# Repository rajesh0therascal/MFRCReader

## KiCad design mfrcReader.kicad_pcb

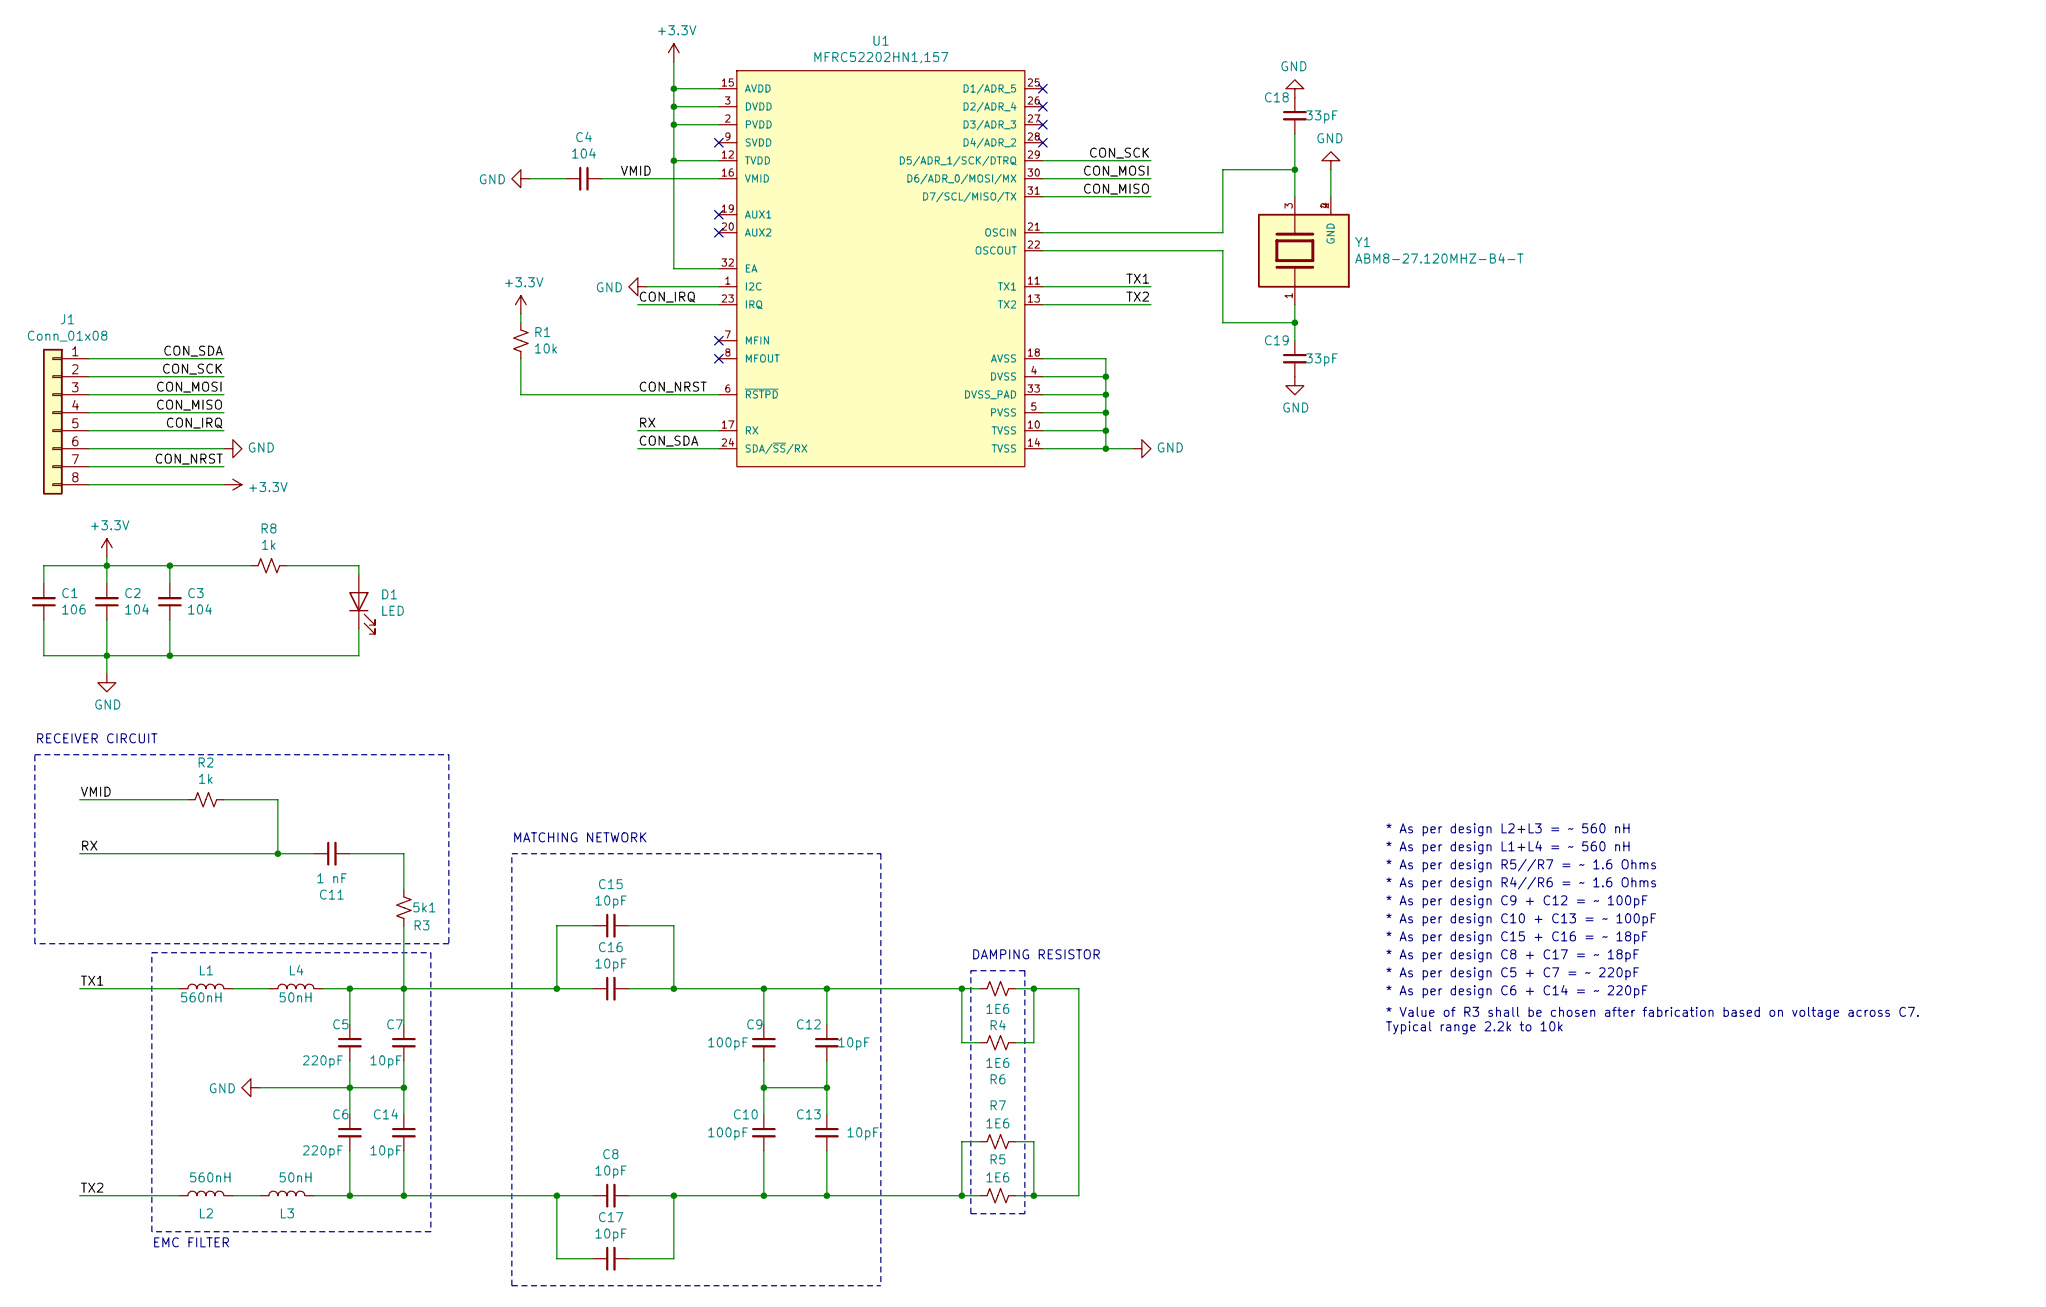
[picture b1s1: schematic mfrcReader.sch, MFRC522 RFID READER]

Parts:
C1: 106; C_0805_2012Metric_Pad1.15x1.40mm_HandSolder
C2, C3, C4: 104; C_0805_2012Metric_Pad1.15x1.40mm_HandSolder
C5, C6: 220pF; C_0805_2012Metric_Pad1.15x1.40mm_HandSolder
C7, C8, C12, C13, C14, C15, C16, C17: 10pF; C_0805_2012Metric_Pad1.15x1.40mm_HandSolder
C9, C10: 100pF; C_0805_2012Metric_Pad1.15x1.40mm_HandSolder
C11: 1 nF; C_0805_2012Metric_Pad1.15x1.40mm_HandSolder
C18, C19: 33pF; C_0805_2012Metric_Pad1.15x1.40mm_HandSolder
D1: LED; D_0805_2012Metric_Pad1.15x1.40mm_HandSolder
J1: Conn_01x08; PinHeader_1x08_P2.54mm_Vertical
L1, L2: 560nH; L_0805_2012Metric_Pad1.15x1.40mm_HandSolder
L3, L4: 50nH; L_0805_2012Metric_Pad1.15x1.40mm_HandSolder
R1: 10k; R_0805_2012Metric_Pad1.15x1.40mm_HandSolder
R2, R8: 1k; R_0805_2012Metric_Pad1.15x1.40mm_HandSolder
R3: 5k1; R_0805_2012Metric_Pad1.15x1.40mm_HandSolder
R4, R5, R6, R7: 1E6; R_0805_2012Metric_Pad1.15x1.40mm_HandSolder
U1: MFRC52202HN1,157; NXP-SOT617-1-0-0-0; mouser part number 771-MFRC52202HN1157; digikey description IC READER 32-HVQFN
Y1: ABM8-27.120MHZ-B4-T; XTAL_ABM8-27.120MHZ-B4-T; PARTREV 44041

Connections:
+3V3: C1.2, C2.2, C3.2, J1.8, R1.2, R8.1, U1.2 (PVDD), U1.3 (DVDD), U1.12 (TVDD), U1.15 (AVDD), U1.32 (EA)
/CON_IRQ: J1.5, U1.23 (IRQ)
/CON_MISO: J1.4, U1.31 (D7/SCL/MISO/TX)
/CON_MOSI: J1.3, U1.30 (D6/ADR_0/MOSI/MX)
/CON_NRST: J1.7, R1.1, U1.6 (~RSTPD~)
/CON_SCK: J1.2, U1.29 (D5/ADR_1/SCK/DTRQ)
/CON_SDA: J1.1, U1.24 (SDA/~SS~/RX)
/RX: C11.1, R2.2, U1.17 (RX)
/TX1: L1.1, U1.11 (TX1)
/TX2: L2.1, U1.13 (TX2)
/VMID: C4.1, R2.1, U1.16 (VMID)
GND: C1.1, C2.1, C3.1, C4.2, C5.2, C6.1, C7.2, C14.1, C18.1, C19.2, D1.1 (K), J1.6, U1.1 (I2C), U1.4 (DVSS), U1.5 (PVSS), U1.10 (TVSS), U1.14 (TVSS), U1.18 (AVSS), U1.33 (DVSS_PAD), Y1.2 (GND), Y1.4 (GND)
unnamed: C9.2, C10.1, C12.2, C13.1
unnamed: C8.2, C10.2, C13.2, C17.2, R5.2, R7.2
unnamed: C11.2, R3.1
unnamed: C9.1, C12.1, C15.2, C16.2, R4.2, R6.2
unnamed: C6.2, C8.1, C14.2, C17.1, L3.2
unnamed: C5.1, C7.1, C15.1, C16.1, L4.2, R3.2
unnamed: C18.2, U1.21 (OSCIN), Y1.3
unnamed: C19.1, U1.22 (OSCOUT), Y1.1
unnamed: D1.2 (A), R8.2
unnamed: L1.2, L4.1
unnamed: L2.2, L3.1
unnamed: R4.1, R5.1, R6.1, R7.1

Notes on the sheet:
RECEIVER CIRCUIT
* As per design R4//R6 = ~~ 1.6 Ohms
* As per design R5//R7 = ~~ 1.6 Ohms
* As per design C9 + C12 = ~~ 100pF
* As per design C10 + C13 = ~~ 100pF
* As per design C15 + C16 = ~~ 18pF
* As per design C8 + C17 = ~~ 18pF
* As per design C5 + C7 = ~~ 220pF
* As per design C6 + C14 = ~~ 220pF
* As per design L1+L4 = ~~ 560 nH
* As per design L2+L3 = ~~ 560 nH
* Value of R3 shall be chosen after fabrication based on voltage across C7. Typical range 2.2k to 10k
EMC FILTER
MATCHING NETWORK
DAMPING RESISTOR

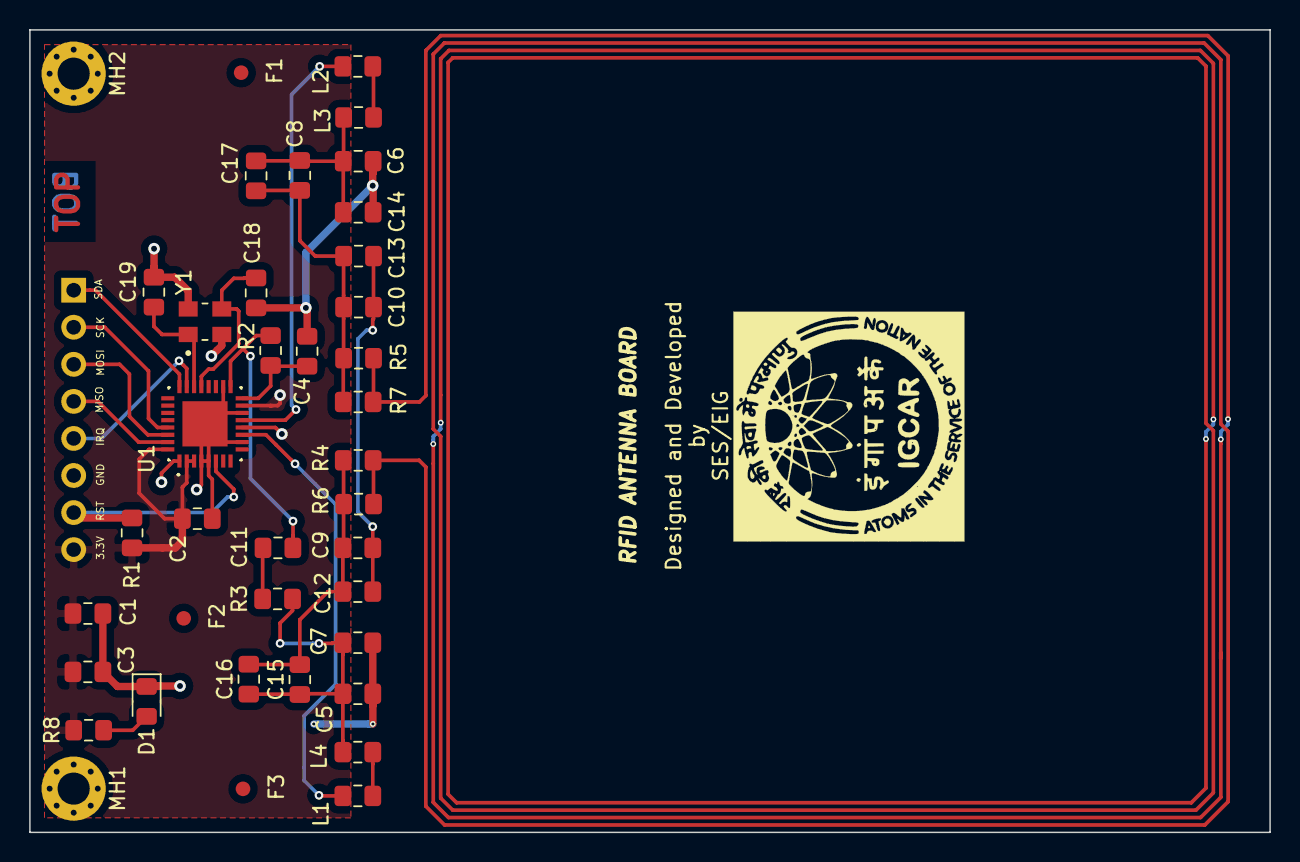
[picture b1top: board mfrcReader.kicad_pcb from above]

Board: 2 copper layers, 85.0 x 55.0 mm, 40 parts (1 on the bottom side), 24 nets.

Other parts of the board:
F1, F2, F3: Fid; Fiducial_1mm_Mask2mm
MH1, MH2: MH; MountingHole_2.2mm_M2_Pad_Via

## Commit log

2022-12-29 Added Files
    First Commit
2022-12-29 Installation scheme for 83 mm reader
2023-01-06 Added Gerber Files
2023-05-12 Centre Cutout
    Added gerber and layout files for center cutout
